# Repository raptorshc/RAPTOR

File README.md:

# RAPTOR

![alt text](https://lh3.googleusercontent.com/3F7HX2s3Zzlc5sHWqSpdH3c7h7buRGXZ99VHywgVTpymfuJBW6MyA9buEFgS44PCumAiEiuxabHniSpxqrTaVh5J7jwUhb6GCc9CwGKvyvS7ThwzLxqMXJqgpR13Qj8XujUiCOFQOPVCgI5XWqbdxXIeXNwvYMKYlWc3gd5bdRVvJ00be6B11PBJqXsWTd11I3m5HuztoBnco_kylwTjR_31pB-0WslzyYl2C6yfqHBNJOgVv58VBqYlOO7VDhNR66DFx0sk-PIVKSzZ8nEvLHmFxbv9pba2LK7mznyDnhQOLP4tlAK3rfnm61t2z8i5NM2hZNphA8zugoPHqHSAXqElzJBOsrFc-QNgnTngvp_hD6V4fl9Tu4M8pO6f3ZDzLxNwsGkESvWQO3hThg58zeGCnwpbbYDFeK5apQqRY_3YjNmyV4v6GxGTtz9Ox8Rz7EK0yaXD61EuavV-B0C2EPOzBIEx0foYOhT-CfNB2nu9g0Fbobc5qj9KgGPJDqf73QYTJpSFaNhnmxSj3N1YVouG3C93t5qZz7imrg0RePZnBkEPyKa7PUGXny-YaL6d6dZhhzWAyaGT50DmVLFzTQHRHtSraFoeSSQYl8YMCDj51ZJ_Kl5lJ4wnVmfkWuiIbS08Pt7EvOpegeyiA6so9muHFtj5YBNILHn9_hr631G31mujGW69gRPxfb-EWtJVl8Ni6no0AfistKcv0Dwtcuisww=w609-h380-no "RAPTOR in Flight")

The **Ram-Air Parafoil Targeted Object Return** (RAPTOR) system is an autonomous payload designed for the simplification of high-altitude balloon payload recovery.

This repository contains links to the mechanical, hardware, and software submodules, as well as balloon flight data and analysis. Posters, papers, and presentations made for RAPTOR are located in the 'information' folder. Please refer to our [2019 VBS Poster](https://github.com/raptorshc/RAPTOR/blob/master/information/posters/RAPTOR%20VBS%20Poster.pdf) for the most up to date summary of the project.

Highlight Album: https://photos.app.goo.gl/u5n21Q6Yy1JVBrjy5

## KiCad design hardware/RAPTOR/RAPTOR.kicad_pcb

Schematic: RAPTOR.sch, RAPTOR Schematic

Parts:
D8, D9: DIODE-1N4148
J1: SOLC_CONN; Molex-2pin
J2: SOLP_CONN; Molex-2pin
J3: JST_2MM_MALE; 2_Pin_Connector
J4: CONN_LED_FIX; Molex-2pin
J5: CONN_SOLP_LED; Molex-2pin
J6: CONN_SOLC_LED; Molex-2pin
J7: EXT_LED0; Molex-2pin
J8: EXT_LED1; Molex-2pin
J9: EXT_LED2; Molex-2pin
J10: EXT_LED3; Molex-2pin
J11: SRVOL_CONN; Molex-MOTOR
J12: SRVOR_CONN; Molex-MOTOR
J13: HOTWIRE_CONN; Molex-2pin
J14: RBF_CONN; Molex-2pin
J15: EEPROM_BTN_CONN; Molex-2pin
J16: SOLC_SW_CONN; Molex-2pin
J17: SOLP_SW_CONN; Molex-2pin
J18: CONN_BUZZER; Molex-2pin
JP1, JP2: Jumper
P1: Power; Socket_Strip_Arduino_1x08
P2: Analog; Arduino_Analog_06
P3: Digital; Arduino_x10_Digital
P4: Digital; Arduino_x08_Digital
P5, P6, P7, P8: CONN_01X01; Arduino_1pin
Q1, Q2, Q3, Q4, Q5: MOSFET-NCH-STQ2NK60ZR-AP; MOSFET
R1: 20OHM-0603-1_10W-1%; Resistor
R2, R3, R4: 100OHM-0603-1_10W-1%; Resistor
R5, R6, R7, R8: 4.7KOHM-0603-1_10W-1%; Resistor
U1: BMP280 Breakout; BMP280
U2: BNO055 Breakout; BNO055
U3: OpenLog
U4: AdafruitGPS
U5: U3V12F12
U6: D24V550F5; D24v50f5_Reg

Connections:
+3V3: P1.4, R1.1
+5V: J11.2, J12.2, J15.1, J16.1, J17.1, J18.1, P1.5, U1.1 (VIN), U2.1 (VIN), U3.4 (VCC), U4.8 (VIN), U6.5 (VOUT)
+7.5V: J13.1, J14.2, P1.8, U5.3 (IN), U6.2 (VIN)
+12V: D8.C, D9.C, J1.1, J2.1, U5.1 (OUT)
/A4(SDA): P3.A4(SDA)
/A5(SCL): P3.A5(SCL)
/AREF: P3.AREF
/BZZ_DTA: P3.11(**/MOSI), Q3.1 (G)
/EEPROM_BTN: J15.2, P4.7, R5.1
/FIX_LED: R2.2, U4.4 (FIX)
/GPS_RX: P4.2, U4.6 (RX)
/GPS_TX: P4.3(**), U4.5 (TX)
/HOTWIRE: P4.4, Q5.1 (G)
/I2C_SCL: P2.A5(SCL), U1.4 (SCK), U2.5 (SCL)
/I2C_SDA: P2.A4(SDA), U1.6 (SDI), U2.4 (SDA)
/IOREF: P1.2
/LEDC_DTA: P2.A3, R4.2
/LEDP_DTA: P2.A2, R3.2
/LEDS_DTA: P3.12(MISO), Q4.1 (G)
/Reset: P1.3
/SD_RX: P4.1(Tx); also elsewhere on the board
/SD_TX: P4.0(Rx); also elsewhere on the board
/SOLC_DTA: P3.8, Q2.1 (G)
/SOLC_SW: J16.2, P2.A1, R6.1
/SOLP_DTA: P3.9(**), Q1.1 (G)
/SOLP_SW: J17.2, P2.A0, R7.1
/SRVO_L: J11.1, P4.5(**)
/SRVO_R: J12.1, P4.6(**)
GND: J3.1 (-), J4.1, J5.1, J6.1, J11.3, J12.3, P1.6, P1.7, P3.GND, Q1.2 (S), Q2.2 (S), Q3.2 (S), Q4.2 (S), R5.2, R6.2, R7.2, R8.2, U1.3 (GND), U2.3 (GND), U3.5 (GND), U4.7 (GND), U5.2 (GND), U6.3 (GND), U6.4 (GND)
unnamed: D8.A, J1.2, Q2.3 (D)
unnamed: D9.A, J2.2, Q1.3 (D)
unnamed: J4.2, R2.1
unnamed: J5.2, R3.1
unnamed: J6.2, R4.1
unnamed: J7.2, J8.2, J9.1, J10.1, R1.2
unnamed: J7.1, J8.1, J9.2, J10.2, Q4.3 (D)
unnamed: J13.2, Q5.3 (D)
unnamed: J3.2 (+), J14.1
unnamed: J18.2, Q3.3 (D)
unnamed: Q5.2 (S), R8.1
unnamed 47: U3.2 (RXI); also elsewhere on the board
unnamed 48: U3.3 (TXO); also elsewhere on the board

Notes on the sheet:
Holes
Shield for Arduino that uses the same pin disposition like "Uno" board Rev 3.

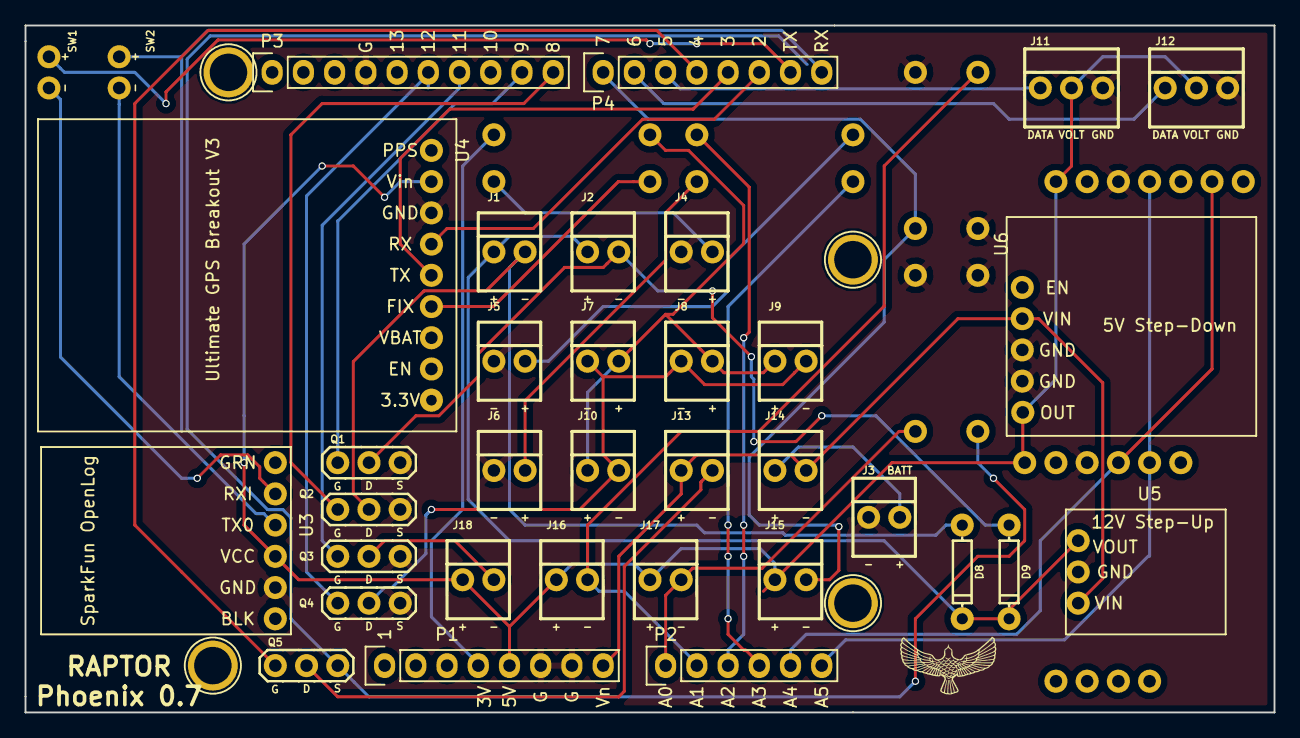
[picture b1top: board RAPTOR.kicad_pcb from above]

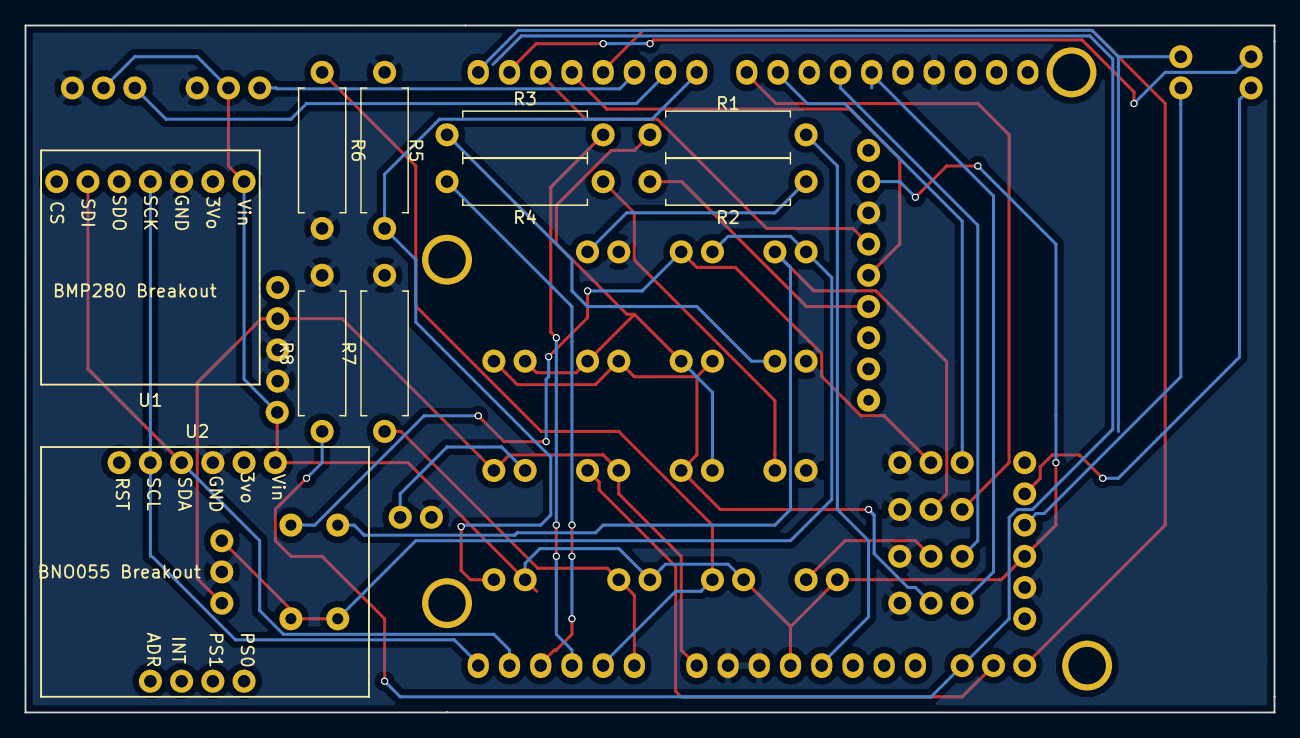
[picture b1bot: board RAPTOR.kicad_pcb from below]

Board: 2 copper layers, 101.6 x 55.9 mm, 49 parts (10 on the bottom side), 37 nets.

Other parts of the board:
SW1, SW2: SW_Push_Open; Jumper

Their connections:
/SD_RX: SW1.2; also elsewhere on the board
/SD_TX: SW2.2; also elsewhere on the board
unnamed 47: SW1.1; also elsewhere on the board
unnamed 48: SW2.1; also elsewhere on the board

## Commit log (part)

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2018-09-19 move to setup
2018-09-19 additional servo testing
2018-09-19 begin implementing superclasses
2018-09-19 implement bmp, gps as subclasses
2018-09-19 alter flight logic
2018-09-20 add test functions, add r and l servos
2018-09-21 add solenoids
2018-09-21 fix errors
2018-09-21 add pilot test function for testing servos
2018-09-21 fix servo pins
2018-09-21 abstract away left/right turn
2018-09-21 add servo status methods
2018-09-21 pilot flying simulation
2018-09-21 fix ifdefs
2018-09-21 additional simulation work
2018-09-22 fix pilot logic
2018-09-22 pilot debugging
2018-09-23 add flight states, change coordinate usage to decimal only
2018-09-23 add to src folder
2018-09-23 fix relative path
2018-09-23 remove update
2018-09-23 remove unnecessary files/folders
2018-09-23 add startup sequence #6
2018-09-23 formatting, resolves #12
2018-09-23 add startup sequence comments, resolves #6
2018-09-24 add py file
2018-09-24 read serial input
2018-09-25 add photos links
2018-09-26 create openlog class
2018-09-26 testing
2018-09-26 use legacy code
2018-09-26 remove comment
2018-09-26 add line verification
2018-09-27 fixed!
2018-09-27 update documentation
2018-09-27 Simupy (#16)
    * add py file
    * read serial input
    * test input and printing
    * testing
    * use legacy code
    * test with file, edit for arduino use
2018-09-27 rermove openlog reset
2018-09-28 add eeprom writing
2018-09-28 debug eeprom
2018-09-28 formatting
2018-09-29 testing and debugging servo
2018-09-30 gps debug
2018-09-30 flight testing and debugging
2018-10-03 add landing check, resolves #24
2018-10-03 formatting, revert some testing specific modfiications
2018-10-03 slightly update readme
2018-10-03 modify deflection setting based on testing
2018-10-05 add reminder
2018-10-05 correct angle
2018-10-05 test deflection setting, debug find turn, resolves #26 resolves #29
2018-10-05 resolves #30
2018-10-06 correct for flight
2018-10-07 Added vector libraries
    Added vector libraries for Arduino. Needs to be tested. This may allow us to keep Skynet in its current form with vectors rather than rewrite a lot of the code with arrays.
2018-10-08 reorganize drivers, add environment class, move functions, formatting
2018-10-08 Patched Arduino vector issue
    Skynet now works with vectors on Arduino. No need to rewrite program using arrays. Must have ArduinoSTL library installed to run. Current issue: Memory usage. defining and training a 3 layer feed for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
2018-10-09 rename folder
2018-10-09 change to actual vector magnitudes, add expected output and number locations
2018-10-09 simplify and refactor pathfinder, resolve #36
2018-10-09 refactor and simplify Pilot
2018-10-13 Add content
2018-10-13 Initial ReadMe Revising (#11)
    * skeleton creation
    * fixes for linting
    * add flight descriptions
    * add photos links
    * Add content
2018-10-13 fix kestral payload interior photo
2018-10-14 add map plotter for generated points
2018-10-14 remove pointgen from class, allow any input
2018-10-14 add main file
2018-10-14 create multiple images
2018-10-14 Revert "Patched Arduino vector issue"
    This reverts commit 5f40a676a6bf3ff4c7e01a88d6d83afa42669503.
2018-10-14 remove redundant file
2018-10-14 Map Plotting (#42)
    * create input generator for Skynet
    * change to actual vector magnitudes, add expected output and number locations
    * add map plotter for generated points
    * add pathing plot, resolve #18
    * remove pointgen from class, allow any input
    * add main file
2018-10-17 Converts BMP data to meters as well as all references to altitude . Resolves issue #40.
2018-10-18 add source for correct_coords function
2018-10-18 add map-plotting folder
2018-10-18 add environments.yml, outputs folder
2018-10-18 remove tight layout, add file printing in main
2018-10-25 new project from arduino uno template
2018-10-25 Revert "put closer to huntsville"
    This reverts commit b5974ddebe3fc5eb5386a9e32f7bf7fedee2eee1.
2018-10-25 create project from arduino mega template with gitignore
2018-10-25 add BMP280 and wiring
2018-10-26 add #defines for target location
2018-10-26 remove testing commenting
2018-10-26 change parafoil deploy altitude
2018-10-26 add bmp footprint
2018-10-26 create hardware, software, flight folders
2018-10-26 reorganize .gitignores to be more local
2018-10-26 add bmp footprint to pcb
2018-10-26 move to uno, re-add bmp
2018-10-27 correct location, add gps alt print
2018-10-27 fix data
2018-10-28 plot map data
2018-10-28 make changes to map plotting
2018-10-30 Initial code update
2018-10-30 Added simulation files
2018-10-30 add inflation delay, resolves #49
2018-10-30 Changed includes.
2018-10-30 Reformatted code.
2018-10-30 Added saving the network to a file.
2018-10-30 Added comments.
2018-10-30 Updated some code in Neuron.cpp
2018-10-30 Corrected an include and made sure it worked.
2018-10-30 Resolved circular includes.
2018-10-30 Implemented activation functions into then neurons.
2018-10-30 Added total number of epochs to train on.
2018-10-30 Made it so that Skynet didn't output only 0's.
2018-10-31 Added helpful comment.
2018-10-31 Changed architecture.
2018-10-31 Changed random function to try to create negative weights.
2018-10-31 Added boolean function to DataLoader to check if there's anymore data to give out.
2018-10-31 Added ways to print database.
2018-10-31 Added generated outputs.
2018-11-01 Fixed data parsing from file.
2018-11-01 Changed how data was generated.
2018-11-01 Simplified topology.
2018-11-01 Added comments and improved checking for empty data.
2018-11-01 Improved checking for no more data.
2018-11-01 Fixed network output.
2018-11-03 Attempted to Change the Bno005 Footprint - didn't go well
2018-11-03 created adafruit gps
2018-11-03 add mp4 and pycache back to overall gitignore
2018-11-04 Added more data to be generated.
2018-11-04 Added more data.
2018-11-04 Starting implementing softmax.
2018-11-06 fixed naming of the open log files and include the SoftwareSerial library from arduino
2018-11-06 fix gps angle
2018-11-08 add print to deploy while, resolves #50
2018-11-09 add comments to bmp, bno, gps
2018-11-09 change comment
2018-11-09 fix pictures, add October flight reports
2018-11-09 Added checking for a good transfer model and printing to an output stream.
2018-11-10 Added all the footprints and associated them with the symbols in the schematics
2018-11-10 fix sensor numbers, add servos, solenoids, leds, switches
2018-11-13 Changed inputting from file a good bit.
2018-11-13 Misc Changes (Comments, printing every 10%, Landing Site clarification)
2018-11-13 add delay after buzz
2018-11-16 set landing coordinates
2019-01-12 First upload of CAD files
2019-01-12 Add voltage regulators, schematic pdf
2019-01-12 Reorganized all of the CAD files for Phoenix
2019-01-12 Uploaded Parafoil frame
2019-01-12 Voltage Reg Footprints
    Created the voltage regulator footprint for he 12v reg
2019-01-12 Auto stash before merge of "hardware" and "origin/hardware"
2019-01-12 rev 0.5.5 schematic
2019-01-12 mosfet source to gnd + sol net label, removed second vreg
    Mosfet was hooked up to -12V, instead added a GND connection and in the middle of source and ground put a wire with a diode going out to a SOLP/C connection. Removed redundant voltage regulator (<0.7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
2019-01-15 change battery to battery connector
2019-01-15 resolves #56
2019-01-15 add pulldown res, resolves #58
2019-01-15 Arduango COnnecter Bois
2019-01-15 Customize Arduino Connectors, add names to net labels, resolve #59
    replace motors with molex connectors
2019-01-16 start uml diagram, add all classes
2019-01-16 added some relationships and attributes/operations
2019-01-16 clarify path relationships, add attributes/operations
2019-01-17 moved a single mosfet
2019-01-17 Fixed MOSFETS gate and drain on diagram
2019-01-17 commit libraries KiCad
2019-01-17 change LED resistor values
2019-01-17 Add seperate Phoenix model for redesign
2019-01-17 make UML changes and refactor accordingly for BMP, GPS
    BMP085 --> BMP280
2019-01-18 fix hotwire
2019-01-18 schematic rev 0.6.5
2019-01-18 Add Electrical Box
2019-01-18 change to D24V550F5
2019-01-18 change pdf
2019-01-18 New V_Reg Footpritnt
    The D24V50F5 has now been added to the Raptor Footprings
2019-01-18 remove capacitors from circuit
2019-01-18 extend board
2019-01-19 Fitted parts
    Placed all the compnents on the actual PCB not just off to the side
2019-01-19 add servo, solenoid, environment
2019-01-19 PCB Error Fixing
    Changed footprints and symbols to be more accurate
2019-01-21 connect a gnd
2019-01-21 Test of mergy bois
    ^^^^
2019-01-21 uml pdf
2019-01-21 Version 1 of fully wired PCB
    A preliminary full connection of the PCB board
2019-01-23 Widened PCB Board
    This should resolve something but IDK the number
2019-01-23 make chungus text
2019-01-24 Revert "Revert "Widened PCB Board""
    This reverts commit edbbf49bd2c69fdd694dc2b23b572114c8313dd8.
2019-01-24 add connector for buzzer, resolves #72
2019-01-24 DeTrced the boi
    See above
2019-01-24 Moved Breakouts to fully on board
    Yeet
2019-01-24 testing silk screen
2019-01-24 moved names on silkscreen and remove long names
2019-01-24 Used many Vias
    Here we go
2019-01-24 Full Wire and Ground Fill
    Also got dem Vias dig dawg.
2019-01-24 fixed silk-screen names again
2019-01-24 updated phoenix PCB pdf diagram
2019-01-26 add backups to gitignore
2019-01-26 fix pdf, add png
2019-01-26 Update Mosfet Vals
    yeet yeet yeet yoote yeet yeet yeet yeet yoote yeet yeet yeet yeet yoote yeet yeet yeet yeet yoote yeet yeet yeet yeet yoote yeet
2019-01-26 oops
    yeah
2019-01-26 Took racy pictures of the PCB
    Don't let them leak to the internet it could ruin her professional career
2019-01-26 Renamed the naughty pics
    Took out of the spaces AN
2019-01-30 Revert "Added Skynet UML"
    This reverts commit 2570f8e27c57858e9ab1f9ac4fc3313ba81188f6.
2019-01-30 add skynet
2019-01-30 move u1, u5 slightly
2019-02-06 refactoring to allow compile
2019-02-07 Begin to unbad openlog class
2019-02-07 REMOVE SNAKECASE AND COMMENTS
2019-02-07 Progress
2019-02-11 generate step
2019-02-11 Added CAD files for the PCB assembled with an Arduino Uno
2019-02-13 Set theme jekyll-theme-cayman
2019-02-14 Attempted some things with openlog
2019-02-22 Additional PCB CAD files
2019-02-22 New Mechanical Release for Actual Parts
    There are 4 new parts files, 1 new assembly file, and a modified Solenoid file.
2019-02-26 Added STL Files for Printing of Bow Release
2019-02-28 3 pin to 2 pin, resolve #90
2019-02-28 Updates to Breakout Board Footprints
2019-02-28 move R2 and R3, resolves #88
2019-02-28 Add Labels to Arduino Uno Headers
2019-02-28 Added footprint for 2-pin molex connector
2019-02-28 add sparkfun libraries
2019-02-28 add mosfet silkscreen, update pcb
2019-02-28 add 2 pin molex and motor silkscreen, resolves #92
2019-02-28 change resistor hole sizes to be consistent
2019-02-28 Organized PCB Layout
2019-03-01 add buttons to rx and tx lines
2019-03-01 Start the Routing
    Lets Go dude
2019-03-01 All Routed w/o RXTX button
    All the connections are made except for the rx and tx button
2019-03-01 Changed trigger holder and added another hole
2019-03-01 make jumper just two pin holes
2019-03-01 BIRD
    BIRD
2019-03-01 did some stuff
2019-03-01 move labels for motors
2019-03-04 Updated Base of Bow Release, added STL files for printing
2019-03-04 invert long input, fix path plotter
2019-03-04 switch to google tiles
2019-03-06 Add Battery Mount for Tenergy
2019-03-06 make map prettier, add venv
2019-03-06 make map prettier
2019-03-06 add requirements.txt'
2019-03-11 add eeprom class, optimize dependencies
2019-03-11 actually add eeprom class
2019-03-11 add test file, rc_test function
2019-03-13 add test stuff
2019-03-15 fix gps interrupt, public environment
2019-03-15 fix pilot turning logic
2019-03-15 finish rc testing things
2019-03-29 Updated Base of Bow Release, added STL files for printing
    Change to Base, adjust Base 2 file location for solenoid
2019-04-08 attempt to debug GPS
2019-04-08 update schematic pdf, pcb picture
2019-04-12 Mechanical Update 4/11
    Add Connecting rod 4A and 4B for 45 degrees solenoid offset. Updated Base 3.
2019-04-13 Mechanical Update 4/13
    Adjust Primary Cutdown Assembly, added ConnectingArm 4A and 4B. Modified ConnectingArm4A, adjusting for width of trigger.
2019-05-06 Updated Release Mechanism
2019-05-06 uncomment stuff that works fine
2019-05-06 fixed time_elapsed
2019-05-07 Added UNO, Shield and Battery Mount
2019-06-06 removed old folders
2019-08-24 Mechanical Update 8/24/19
    Add Single Servo Mount asm
2019-08-26 add vbs poster to readme
2019-08-26 add vbs hyperlink
